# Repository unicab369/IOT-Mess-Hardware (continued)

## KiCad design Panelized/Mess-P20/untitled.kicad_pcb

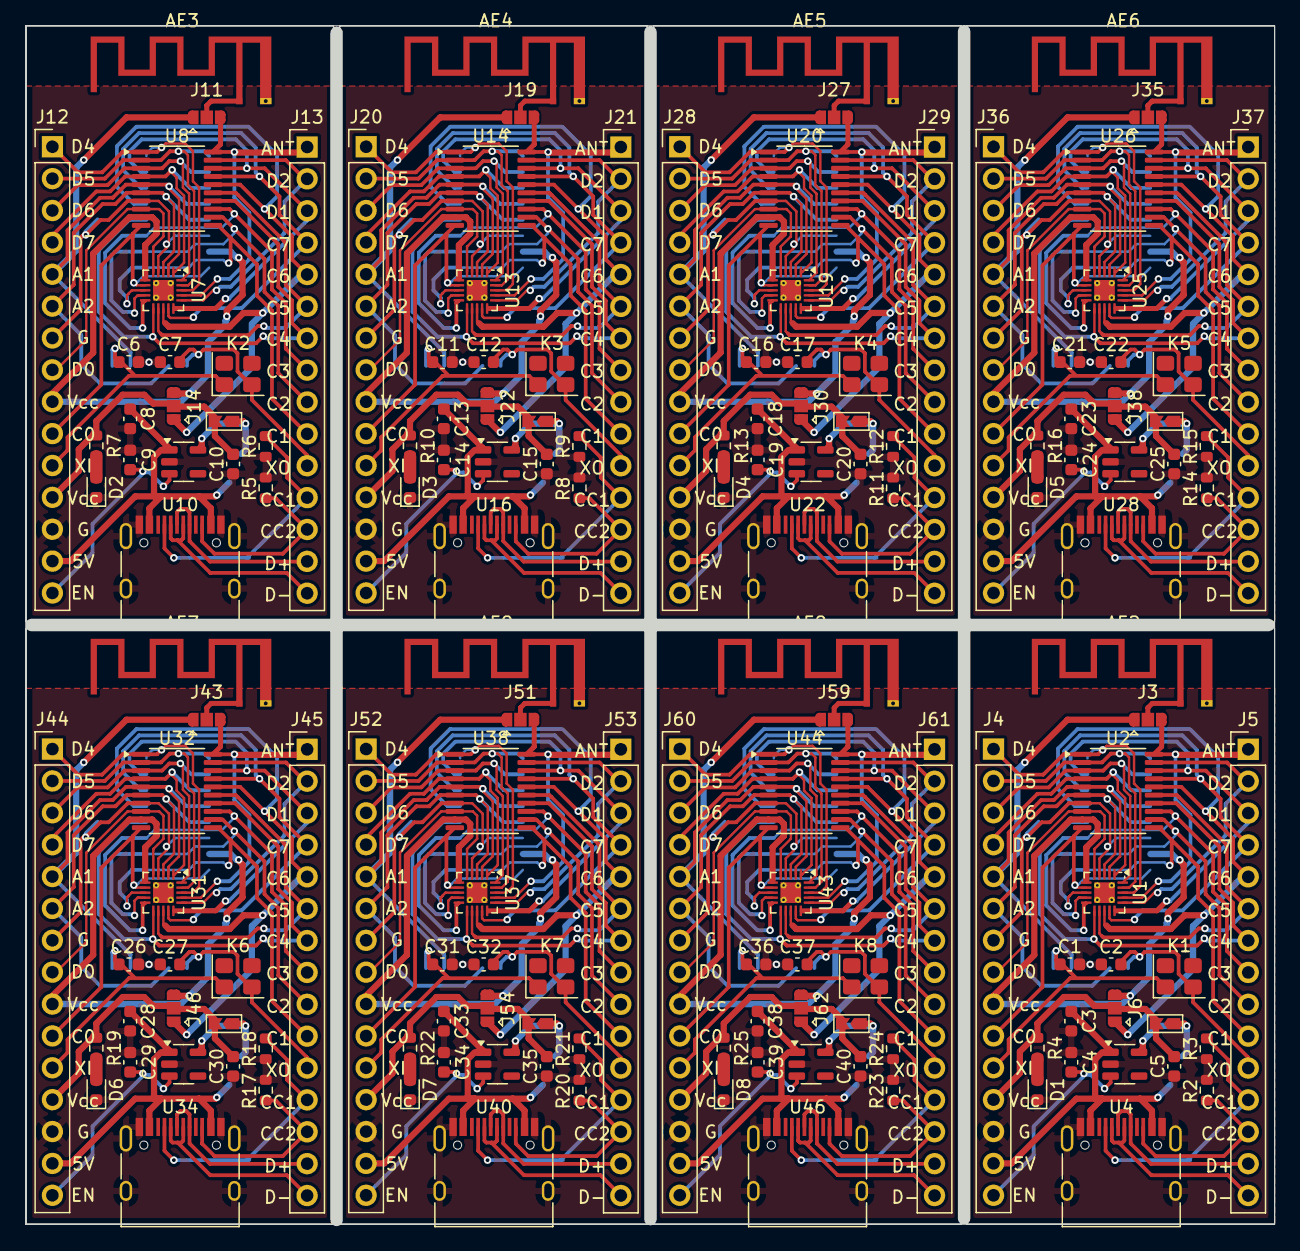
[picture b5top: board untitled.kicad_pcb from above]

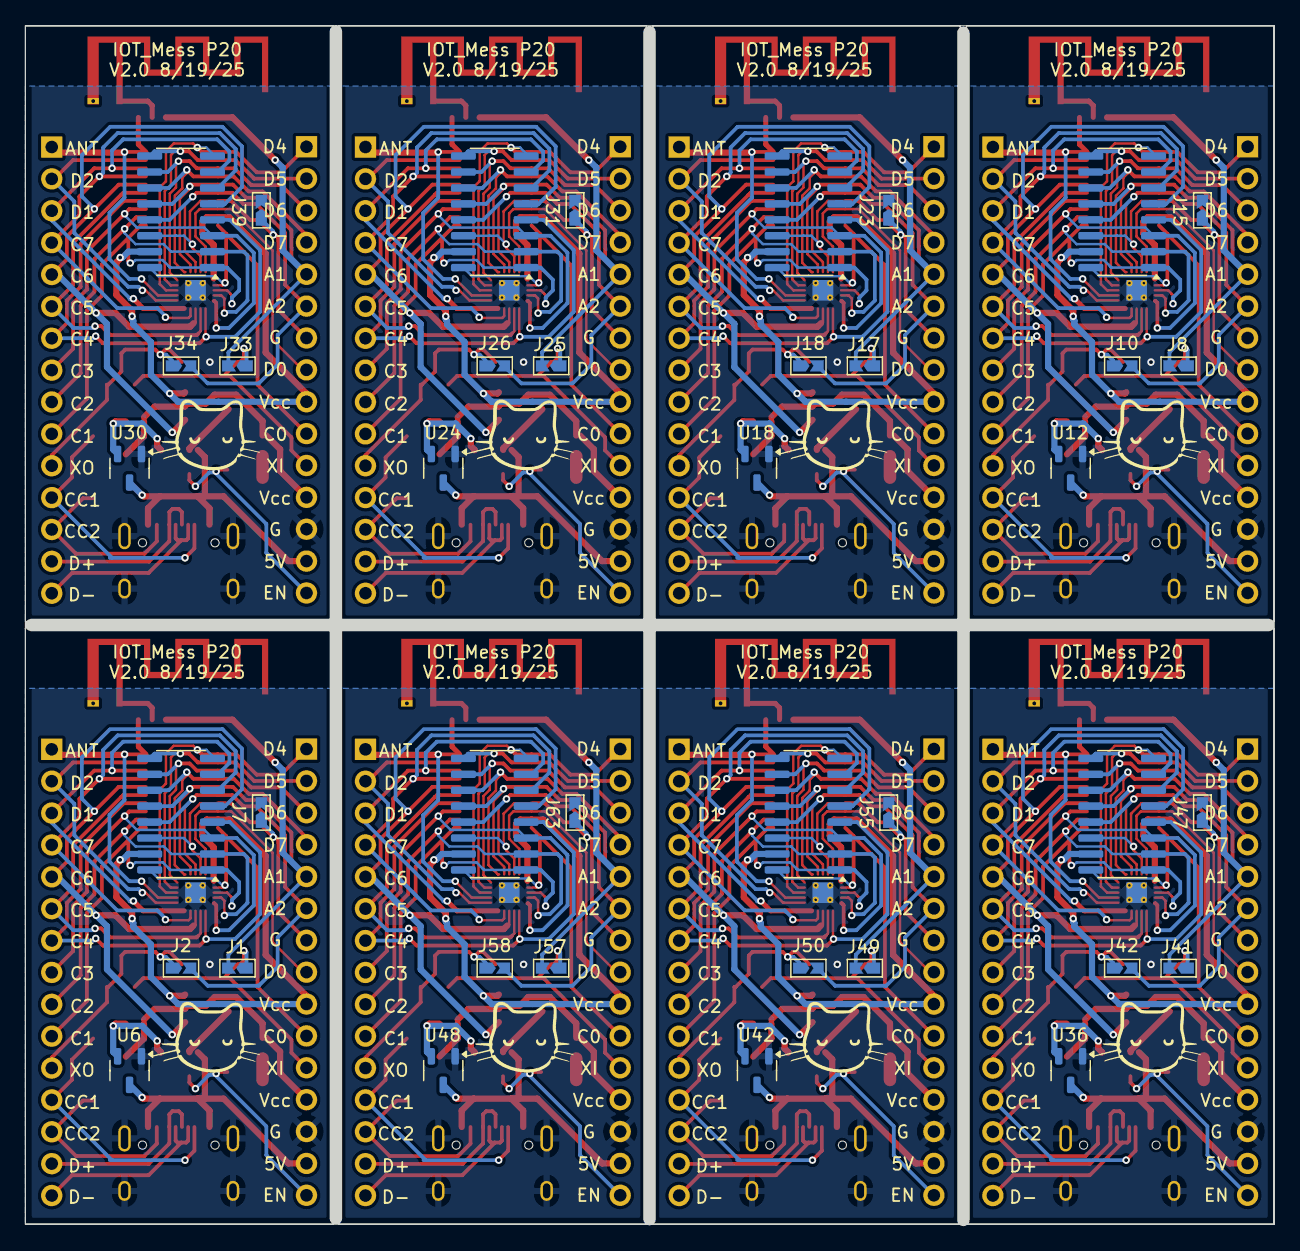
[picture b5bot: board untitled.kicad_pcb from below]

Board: 2 copper layers, 99.5 x 95.5 mm, 200 parts (40 on the bottom side), 33 nets.

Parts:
AE2, AE3, AE4, AE5, AE6, AE7, AE8, AE9: Antenna_Shield; Texas_SWRA117D_2.4GHz_Left
C1, C2, C6, C7, C11, C12, C16, C17, C21, C22, C26, C27, C31, C32, C36, C37: 12-25pF; C_0603_1608Metric
C3, C8, C13, C18, C23, C28, C33, C38: 10u; C_0603_1608Metric
C4, C5, C9, C10, C14, C15, C19, C20, C24, C25, C29, C30, C34, C35, C39, C40: 1u; C_0603_1608Metric
D1, D2, D3, D4, D5, D6, D7, D8: LED; LED_0603_1608Metric
J1, J2, J7, J8, J9, J10, J15, J16, J17, J18, J23, J24, J25, J26, J31, J32, J33, J34, J39, J40, J41, J42, J47, J48, J49, J50, J55, J56, J57, J58, J63, J64: Jumper_2; Jumpper-triangle
J3, J6, J11, J14, J19, J22, J27, J30, J35, J38, J43, J46, J51, J54, J59, J62: Jumper; Jumper-3_P1.3mm_Open_RoundedPad1.0x1.5mm
J4, J5, J12, J13, J20, J21, J28, J29, J36, J37, J44, J45, J52, J53, J60, J61: Conn_01x15_Pin; PinHeader_1x15_P2.54mm_Vertical
K1, K2, K3, K4, K5, K6, K7, K8: Crystal; Crystal_SMD_3225-4Pin_3.2x2.5mm
R2, R3, R5, R6, R8, R9, R11, R12, R14, R15, R17, R18, R20, R21, R23, R24: 5.1K; R_0603_1608Metric
R4, R7, R10, R13, R16, R19, R22, R25: R; R_0603_1608Metric
U1, U7, U13, U19, U25, U31, U37, U43: QFN-20-1EP_3x3mm_P0.4mm_EP1.65x1.65mm_ThermalVias
U2, U8, U14, U20, U26, U32, U38, U44: TSSOP-20_4.4x6.5mm_P0.65mm
U3, U9, U15, U21, U27, U33, U39, U45: SOP-16_3.9x9.9mm_P1.27mm
U4, U10, U16, U22, U28, U34, U40, U46: USB_C_Receptacle_USB2.0_16P; USB_C_Receptacle_HRO_TYPE-C-31-M-12
U5, U11, U17, U23, U29, U35, U41, U47: ME6211C33M5; SOT-23-5
U6, U12, U18, U24, U30, U36, U42, U48: XC6206PxxxMR; SOT-23-3

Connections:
5V: C3.1, C8.1, C13.1, C18.1, C23.1, C28.1, C33.1, C38.1, J4.14, J12.14, J20.14, J28.14, J36.14, J44.14, J52.14, J60.14, U4.A4 (VBUS), U4.A9 (VBUS), U4.B4 (VBUS), U4.B9 (VBUS), U5.1 (V_{IN}), U6.3 (VI), U10.A4 (VBUS), U10.A9 (VBUS), U10.B4 (VBUS), U10.B9 (VBUS), U11.1 (V_{IN}), U12.3 (VI), U16.A4 (VBUS), U16.A9 (VBUS), U16.B4 (VBUS), U16.B9 (VBUS), U17.1 (V_{IN}), U18.3 (VI), U22.A4 (VBUS), U22.A9 (VBUS), U22.B4 (VBUS), U22.B9 (VBUS), U23.1 (V_{IN}), U24.3 (VI), U28.A4 (VBUS), U28.A9 (VBUS), U28.B4 (VBUS), U28.B9 (VBUS), U29.1 (V_{IN}), U30.3 (VI), U34.A4 (VBUS), U34.A9 (VBUS), U34.B4 (VBUS), U34.B9 (VBUS), U35.1 (V_{IN}), U36.3 (VI), U40.A4 (VBUS), U40.A9 (VBUS), U40.B4 (VBUS), U40.B9 (VBUS), U41.1 (V_{IN}), U42.3 (VI), U46.A4 (VBUS), U46.A9 (VBUS), U46.B4 (VBUS), U46.B9 (VBUS), U47.1 (V_{IN}), U48.3 (VI)
+3.3V: C5.1, C10.1, C15.1, C20.1, C25.1, C30.1, C35.1, C40.1, J4.12, J6.2 (C), J9.2 (B), J12.12, J14.2 (C), J16.2 (B), J20.12, J22.2 (C), J24.2 (B), J28.12, J30.2 (C), J32.2 (B), J36.12, J38.2 (C), J40.2 (B), J44.12, J46.2 (C), J48.2 (B), J52.12, J54.2 (C), J56.2 (B), J60.12, J62.2 (C), J64.2 (B), R4.1, R7.1, R10.1, R13.1, R16.1, R19.1, R22.1, R25.1
ANT: AE2.1 (A), AE3.1 (A), AE4.1 (A), AE5.1 (A), AE6.1 (A), AE7.1 (A), AE8.1 (A), AE9.1 (A), J3.2 (C), J11.2 (C), J19.2 (C), J27.2 (C), J35.2 (C), J43.2 (C), J51.2 (C), J59.2 (C)
CC1: J5.12, J13.12, J21.12, J29.12, J37.12, J45.12, J53.12, J61.12, R3.1, R6.1, R9.1, R12.1, R15.1, R18.1, R21.1, R24.1, U4.A5 (CC1), U10.A5 (CC1), U16.A5 (CC1), U22.A5 (CC1), U28.A5 (CC1), U34.A5 (CC1), U40.A5 (CC1), U46.A5 (CC1)
CC2: J5.13, J13.13, J21.13, J29.13, J37.13, J45.13, J53.13, J61.13, R2.1, R5.1, R8.1, R11.1, R14.1, R17.1, R20.1, R23.1, U4.B5 (CC2), U10.B5 (CC2), U16.B5 (CC2), U22.B5 (CC2), U28.B5 (CC2), U34.B5 (CC2), U40.B5 (CC2), U46.B5 (CC2)
D+: J5.14, J13.14, J21.14, J29.14, J37.14, J45.14, J53.14, J61.14, U4.A6 (D+), U4.B6 (D+), U10.A6 (D+), U10.B6 (D+), U16.A6 (D+), U16.B6 (D+), U22.A6 (D+), U22.B6 (D+), U28.A6 (D+), U28.B6 (D+), U34.A6 (D+), U34.B6 (D+), U40.A6 (D+), U40.B6 (D+), U46.A6 (D+), U46.B6 (D+)
D-: J5.15, J13.15, J21.15, J29.15, J37.15, J45.15, J53.15, J61.15, U4.A7 (D-), U4.B7 (D-), U10.A7 (D-), U10.B7 (D-), U16.A7 (D-), U16.B7 (D-), U22.A7 (D-), U22.B7 (D-), U28.A7 (D-), U28.B7 (D-), U34.A7 (D-), U34.B7 (D-), U40.A7 (D-), U40.B7 (D-), U46.A7 (D-), U46.B7 (D-)
LDO_EN: C4.1, C9.1, C14.1, C19.1, C24.1, C29.1, C34.1, C39.1, J4.15, J12.15, J20.15, J28.15, J36.15, J44.15, J52.15, J60.15, U5.3 (CE), U11.3 (CE), U17.3 (CE), U23.3 (CE), U29.3 (CE), U35.3 (CE), U41.3 (CE), U47.3 (CE)
unnamed: D1.2 (A), D2.2 (A), D3.2 (A), D4.2 (A), D5.2 (A), D6.2 (A), D7.2 (A), D8.2 (A), R4.2, R7.2, R10.2, R13.2, R16.2, R19.2, R22.2, R25.2
unnamed: J9.1 (A), J16.1 (A), J24.1 (A), J32.1 (A), J40.1 (A), J48.1 (A), J56.1 (A), J64.1 (A), U5.5 (V_{OUT}), U6.2 (VO), U11.5 (V_{OUT}), U12.2 (VO), U17.5 (V_{OUT}), U18.2 (VO), U23.5 (V_{OUT}), U24.2 (VO), U29.5 (V_{OUT}), U30.2 (VO), U35.5 (V_{OUT}), U36.2 (VO), U41.5 (V_{OUT}), U42.2 (VO), U47.5 (V_{OUT}), U48.2 (VO)
OSCI: C1.1, C6.1, C11.1, C16.1, C21.1, C26.1, C31.1, C36.1, J1.1 (A), J4.11, J8.1 (A), J12.11, J17.1 (A), J20.11, J25.1 (A), J28.11, J33.1 (A), J36.11, J41.1 (A), J44.11, J49.1 (A), J52.11, J57.1 (A), J60.11, K1.1, K2.1, K3.1, K4.1, K5.1, K6.1, K7.1, K8.1
OSCO: C2.1, C7.1, C12.1, C17.1, C22.1, C27.1, C32.1, C37.1, J2.1 (A), J5.11, J10.1 (A), J13.11, J18.1 (A), J21.11, J26.1 (A), J29.11, J34.1 (A), J37.11, J42.1 (A), J45.11, J50.1 (A), J53.11, J58.1 (A), J61.11, K1.2, K2.2, K3.2, K4.2, K5.2, K6.2, K7.2, K8.2
P_0: C1.2, C2.2, C3.2, C4.2, C5.2, C6.2, C7.2, C8.2, C9.2, C10.2, C11.2, C12.2, C13.2, C14.2, C15.2, C16.2, C17.2, C18.2, C19.2, C20.2, C21.2, C22.2, C23.2, C24.2, C25.2, C26.2, C27.2, C28.2, C29.2, C30.2, C31.2, C32.2, C33.2, C34.2, C35.2, C36.2, C37.2, C38.2, C39.2, C40.2, D1.1 (K), D2.1 (K), D3.1 (K), D4.1 (K), D5.1 (K), D6.1 (K), D7.1 (K), D8.1 (K), J4.13, J7.2 (B), J12.13, J15.2 (B), J20.13, J23.2 (B), J28.13, J31.2 (B), J36.13, J39.2 (B), J44.13, J47.2 (B), J52.13, J55.2 (B), J60.13, J63.2 (B), R2.2, R3.2, R5.2, R6.2, R8.2, R9.2, R11.2, R12.2, R14.2, R15.2, R17.2, R18.2, R20.2, R21.2, R23.2, R24.2, U1.21 (GND), U4.A1 (GND), U4.A12 (GND), U4.B1 (GND), U4.B12 (GND), U4.S1 (SHIELD), U5.2 (V_{SS}), U6.1 (GND), U7.21 (GND), U10.A1 (GND), U10.A12 (GND), U10.B1 (GND), U10.B12 (GND), U10.S1 (SHIELD), U11.2 (V_{SS}), U12.1 (GND), U13.21 (GND), U16.A1 (GND), U16.A12 (GND), U16.B1 (GND), U16.B12 (GND), U16.S1 (SHIELD), U17.2 (V_{SS}), U18.1 (GND), U19.21 (GND), U22.A1 (GND), U22.A12 (GND), U22.B1 (GND), U22.B12 (GND), U22.S1 (SHIELD), U23.2 (V_{SS}), U24.1 (GND), U25.21 (GND), U28.A1 (GND), U28.A12 (GND), U28.B1 (GND), U28.B12 (GND), U28.S1 (SHIELD), U29.2 (V_{SS}), U30.1 (GND), U31.21 (GND), U34.A1 (GND), U34.A12 (GND), U34.B1 (GND), U34.B12 (GND), U34.S1 (SHIELD), U35.2 (V_{SS}), U36.1 (GND), U37.21 (GND), U40.A1 (GND), U40.A12 (GND), U40.B1 (GND), U40.B12 (GND), U40.S1 (SHIELD), U41.2 (V_{SS}), U42.1 (GND), U43.21 (GND), U46.A1 (GND), U46.A12 (GND), U46.B1 (GND), U46.B12 (GND), U46.S1 (SHIELD), U47.2 (V_{SS}), U48.1 (GND)
P_1: J4.1, J12.1, J20.1, J28.1, J36.1, J44.1, J52.1, J60.1, U1.18 (PD4/A7), U2.1 (PD4/A7), U3.8 (PD4/A7), U7.18 (PD4/A7), U8.1 (PD4/A7), U9.8 (PD4/A7), U13.18 (PD4/A7), U14.1 (PD4/A7), U15.8 (PD4/A7), U19.18 (PD4/A7), U20.1 (PD4/A7), U21.8 (PD4/A7), U25.18 (PD4/A7), U26.1 (PD4/A7), U27.8 (PD4/A7), U31.18 (PD4/A7), U32.1 (PD4/A7), U33.8 (PD4/A7), U37.18 (PD4/A7), U38.1 (PD4/A7), U39.8 (PD4/A7), U43.18 (PD4/A7), U44.1 (PD4/A7), U45.8 (PD4/A7)
P_2: J4.2, J12.2, J20.2, J28.2, J36.2, J44.2, J52.2, J60.2, U1.19 (PD5/A5/UTX/VDD*), U2.2 (PD5/A5/OSCI*), U3.9 (PD5/A5/UTX), U7.19 (PD5/A5/UTX/VDD*), U8.2 (PD5/A5/OSCI*), U9.9 (PD5/A5/UTX), U13.19 (PD5/A5/UTX/VDD*), U14.2 (PD5/A5/OSCI*), U15.9 (PD5/A5/UTX), U19.19 (PD5/A5/UTX/VDD*), U20.2 (PD5/A5/OSCI*), U21.9 (PD5/A5/UTX), U25.19 (PD5/A5/UTX/VDD*), U26.2 (PD5/A5/OSCI*), U27.9 (PD5/A5/UTX), U31.19 (PD5/A5/UTX/VDD*), U32.2 (PD5/A5/OSCI*), U33.9 (PD5/A5/UTX), U37.19 (PD5/A5/UTX/VDD*), U38.2 (PD5/A5/OSCI*), U39.9 (PD5/A5/UTX), U43.19 (PD5/A5/UTX/VDD*), U44.2 (PD5/A5/OSCI*), U45.9 (PD5/A5/UTX)
P_3: J4.3, J12.3, J20.3, J28.3, J36.3, J44.3, J52.3, J60.3, U1.20 (PD6/A6/URX/ANT*), U2.3 (PD6/A6/OSCO*), U3.10 (PD6/A6/URX), U7.20 (PD6/A6/URX/ANT*), U8.3 (PD6/A6/OSCO*), U9.10 (PD6/A6/URX), U13.20 (PD6/A6/URX/ANT*), U14.3 (PD6/A6/OSCO*), U15.10 (PD6/A6/URX), U19.20 (PD6/A6/URX/ANT*), U20.3 (PD6/A6/OSCO*), U21.10 (PD6/A6/URX), U25.20 (PD6/A6/URX/ANT*), U26.3 (PD6/A6/OSCO*), U27.10 (PD6/A6/URX), U31.20 (PD6/A6/URX/ANT*), U32.3 (PD6/A6/OSCO*), U33.10 (PD6/A6/URX), U37.20 (PD6/A6/URX/ANT*), U38.3 (PD6/A6/OSCO*), U39.10 (PD6/A6/URX), U43.20 (PD6/A6/URX/ANT*), U44.3 (PD6/A6/OSCO*), U45.10 (PD6/A6/URX)
P_4: J4.4, J12.4, J20.4, J28.4, J36.4, J44.4, J52.4, J60.4, U1.1 (PD7/NRST), U2.4 (PD7/RST), U3.11 (PD7/NRST), U7.1 (PD7/NRST), U8.4 (PD7/RST), U9.11 (PD7/NRST), U13.1 (PD7/NRST), U14.4 (PD7/RST), U15.11 (PD7/NRST), U19.1 (PD7/NRST), U20.4 (PD7/RST), U21.11 (PD7/NRST), U25.1 (PD7/NRST), U26.4 (PD7/RST), U27.11 (PD7/NRST), U31.1 (PD7/NRST), U32.4 (PD7/RST), U33.11 (PD7/NRST), U37.1 (PD7/NRST), U38.4 (PD7/RST), U39.11 (PD7/NRST), U43.1 (PD7/NRST), U44.4 (PD7/RST), U45.11 (PD7/NRST)
P_5: J1.2 (B), J3.1 (A), J4.5, J8.2 (B), J11.1 (A), J12.5, J17.2 (B), J19.1 (A), J20.5, J25.2 (B), J27.1 (A), J28.5, J33.2 (B), J35.1 (A), J36.5, J41.2 (B), J43.1 (A), J44.5, J49.2 (B), J51.1 (A), J52.5, J57.2 (B), J59.1 (A), J60.5, U1.2 (PA1/OSCI), U2.5 (PA1/OSCI), U3.12 (PA1/A1/OSC_IN), U7.2 (PA1/OSCI), U8.5 (PA1/OSCI), U9.12 (PA1/A1/OSC_IN), U13.2 (PA1/OSCI), U14.5 (PA1/OSCI), U15.12 (PA1/A1/OSC_IN), U19.2 (PA1/OSCI), U20.5 (PA1/OSCI), U21.12 (PA1/A1/OSC_IN), U25.2 (PA1/OSCI), U26.5 (PA1/OSCI), U27.12 (PA1/A1/OSC_IN), U31.2 (PA1/OSCI), U32.5 (PA1/OSCI), U33.12 (PA1/A1/OSC_IN), U37.2 (PA1/OSCI), U38.5 (PA1/OSCI), U39.12 (PA1/A1/OSC_IN), U43.2 (PA1/OSCI), U44.5 (PA1/OSCI), U45.12 (PA1/A1/OSC_IN)
P_6: J2.2 (B), J4.6, J10.2 (B), J12.6, J18.2 (B), J20.6, J26.2 (B), J28.6, J34.2 (B), J36.6, J42.2 (B), J44.6, J50.2 (B), J52.6, J58.2 (B), J60.6, U1.3 (PA2/OSCO), U2.6 (PA2/OSCO), U3.13 (PA2/A0/OSC_OUT), U7.3 (PA2/OSCO), U8.6 (PA2/OSCO), U9.13 (PA2/A0/OSC_OUT), U13.3 (PA2/OSCO), U14.6 (PA2/OSCO), U15.13 (PA2/A0/OSC_OUT), U19.3 (PA2/OSCO), U20.6 (PA2/OSCO), U21.13 (PA2/A0/OSC_OUT), U25.3 (PA2/OSCO), U26.6 (PA2/OSCO), U27.13 (PA2/A0/OSC_OUT), U31.3 (PA2/OSCO), U32.6 (PA2/OSCO), U33.13 (PA2/A0/OSC_OUT), U37.3 (PA2/OSCO), U38.6 (PA2/OSCO), U39.13 (PA2/A0/OSC_OUT), U43.3 (PA2/OSCO), U44.6 (PA2/OSCO), U45.13 (PA2/A0/OSC_OUT)
P_7: J4.7, J7.1 (A), J12.7, J15.1 (A), J20.7, J23.1 (A), J28.7, J31.1 (A), J36.7, J39.1 (A), J44.7, J47.1 (A), J52.7, J55.1 (A), J60.7, J63.1 (A), U1.4 (VSS), U2.7 (VSS), U3.14 (GND), U7.4 (VSS), U8.7 (VSS), U9.14 (GND), U13.4 (VSS), U14.7 (VSS), U15.14 (GND), U19.4 (VSS), U20.7 (VSS), U21.14 (GND), U25.4 (VSS), U26.7 (VSS), U27.14 (GND), U31.4 (VSS), U32.7 (VSS), U33.14 (GND), U37.4 (VSS), U38.7 (VSS), U39.14 (GND), U43.4 (VSS), U44.7 (VSS), U45.14 (GND)
P_8: J4.8, J12.8, J20.8, J28.8, J36.8, J44.8, J52.8, J60.8, U1.5 (PD0/ANT*(57x)), U2.8 (PD0), U7.5 (PD0/ANT*(57x)), U8.8 (PD0), U13.5 (PD0/ANT*(57x)), U14.8 (PD0), U19.5 (PD0/ANT*(57x)), U20.8 (PD0), U25.5 (PD0/ANT*(57x)), U26.8 (PD0), U31.5 (PD0/ANT*(57x)), U32.8 (PD0), U37.5 (PD0/ANT*(57x)), U38.8 (PD0), U43.5 (PD0/ANT*(57x)), U44.8 (PD0)
P_9: J4.9, J6.3 (B), J12.9, J14.3 (B), J20.9, J22.3 (B), J28.9, J30.3 (B), J36.9, J38.3 (B), J44.9, J46.3 (B), J52.9, J54.3 (B), J60.9, J62.3 (B), U1.6 (VDD), U2.9 (VDD), U3.15 (VDD), U7.6 (VDD), U8.9 (VDD), U9.15 (VDD), U13.6 (VDD), U14.9 (VDD), U15.15 (VDD), U19.6 (VDD), U20.9 (VDD), U21.15 (VDD), U25.6 (VDD), U26.9 (VDD), U27.15 (VDD), U31.6 (VDD), U32.9 (VDD), U33.15 (VDD), U37.6 (VDD), U38.9 (VDD), U39.15 (VDD), U43.6 (VDD), U44.9 (VDD), U45.15 (VDD)
P_10: J4.10, J12.10, J20.10, J28.10, J36.10, J44.10, J52.10, J60.10, U1.7 (PC0), U2.10 (PC0), U3.16 (PC0), U7.7 (PC0), U8.10 (PC0), U9.16 (PC0), U13.7 (PC0), U14.10 (PC0), U15.16 (PC0), U19.7 (PC0), U20.10 (PC0), U21.16 (PC0), U25.7 (PC0), U26.10 (PC0), U27.16 (PC0), U31.7 (PC0), U32.10 (PC0), U33.16 (PC0), U37.7 (PC0), U38.10 (PC0), U39.16 (PC0), U43.7 (PC0), U44.10 (PC0), U45.16 (PC0)
P_11: J5.10, J13.10, J21.10, J29.10, J37.10, J45.10, J53.10, J61.10, U1.8 (PC1/SDA), U2.11 (PC1/SDA), U3.1 (PC1/SDA), U7.8 (PC1/SDA), U8.11 (PC1/SDA), U9.1 (PC1/SDA), U13.8 (PC1/SDA), U14.11 (PC1/SDA), U15.1 (PC1/SDA), U19.8 (PC1/SDA), U20.11 (PC1/SDA), U21.1 (PC1/SDA), U25.8 (PC1/SDA), U26.11 (PC1/SDA), U27.1 (PC1/SDA), U31.8 (PC1/SDA), U32.11 (PC1/SDA), U33.1 (PC1/SDA), U37.8 (PC1/SDA), U38.11 (PC1/SDA), U39.1 (PC1/SDA), U43.8 (PC1/SDA), U44.11 (PC1/SDA), U45.1 (PC1/SDA)
P_12: J5.9, J13.9, J21.9, J29.9, J37.9, J45.9, J53.9, J61.9, U1.9 (PC2/SCL), U2.12 (PC2/SCL), U3.2 (PC2/SCL), U7.9 (PC2/SCL), U8.12 (PC2/SCL), U9.2 (PC2/SCL), U13.9 (PC2/SCL), U14.12 (PC2/SCL), U15.2 (PC2/SCL), U19.9 (PC2/SCL), U20.12 (PC2/SCL), U21.2 (PC2/SCL), U25.9 (PC2/SCL), U26.12 (PC2/SCL), U27.2 (PC2/SCL), U31.9 (PC2/SCL), U32.12 (PC2/SCL), U33.2 (PC2/SCL), U37.9 (PC2/SCL), U38.12 (PC2/SCL), U39.2 (PC2/SCL), U43.9 (PC2/SCL), U44.12 (PC2/SCL), U45.2 (PC2/SCL)
P_13: J5.8, J13.8, J21.8, J29.8, J37.8, J45.8, J53.8, J61.8, U1.10 (PC3/RST*), U2.13 (PC3), U3.3 (PC3), U7.10 (PC3/RST*), U8.13 (PC3), U9.3 (PC3), U13.10 (PC3/RST*), U14.13 (PC3), U15.3 (PC3), U19.10 (PC3/RST*), U20.13 (PC3), U21.3 (PC3), U25.10 (PC3/RST*), U26.13 (PC3), U27.3 (PC3), U31.10 (PC3/RST*), U32.13 (PC3), U33.3 (PC3), U37.10 (PC3/RST*), U38.13 (PC3), U39.3 (PC3), U43.10 (PC3/RST*), U44.13 (PC3), U45.3 (PC3)
P_14: J5.7, J13.7, J21.7, J29.7, J37.7, J45.7, J53.7, J61.7, U1.11 (PC4/A2), U2.14 (PC4/A2), U3.4 (PC4/A2), U7.11 (PC4/A2), U8.14 (PC4/A2), U9.4 (PC4/A2), U13.11 (PC4/A2), U14.14 (PC4/A2), U15.4 (PC4/A2), U19.11 (PC4/A2), U20.14 (PC4/A2), U21.4 (PC4/A2), U25.11 (PC4/A2), U26.14 (PC4/A2), U27.4 (PC4/A2), U31.11 (PC4/A2), U32.14 (PC4/A2), U33.4 (PC4/A2), U37.11 (PC4/A2), U38.14 (PC4/A2), U39.4 (PC4/A2), U43.11 (PC4/A2), U44.14 (PC4/A2), U45.4 (PC4/A2)
P_15: J5.6, J13.6, J21.6, J29.6, J37.6, J45.6, J53.6, J61.6, U1.12 (PC5/X32MO*), U2.15 (PC5/VSS*), U7.12 (PC5/X32MO*), U8.15 (PC5/VSS*), U13.12 (PC5/X32MO*), U14.15 (PC5/VSS*), U19.12 (PC5/X32MO*), U20.15 (PC5/VSS*), U25.12 (PC5/X32MO*), U26.15 (PC5/VSS*), U31.12 (PC5/X32MO*), U32.15 (PC5/VSS*), U37.12 (PC5/X32MO*), U38.15 (PC5/VSS*), U43.12 (PC5/X32MO*), U44.15 (PC5/VSS*)
P_16: J5.5, J6.1 (A), J13.5, J14.1 (A), J21.5, J22.1 (A), J29.5, J30.1 (A), J37.5, J38.1 (A), J45.5, J46.1 (A), J53.5, J54.1 (A), J61.5, J62.1 (A), U1.13 (PC6/MOSI/X32MI*), U2.16 (PC6/MOSI/VDD*), U3.5 (PC6/MOSI), U7.13 (PC6/MOSI/X32MI*), U8.16 (PC6/MOSI/VDD*), U9.5 (PC6/MOSI), U13.13 (PC6/MOSI/X32MI*), U14.16 (PC6/MOSI/VDD*), U15.5 (PC6/MOSI), U19.13 (PC6/MOSI/X32MI*), U20.16 (PC6/MOSI/VDD*), U21.5 (PC6/MOSI), U25.13 (PC6/MOSI/X32MI*), U26.16 (PC6/MOSI/VDD*), U27.5 (PC6/MOSI), U31.13 (PC6/MOSI/X32MI*), U32.16 (PC6/MOSI/VDD*), U33.5 (PC6/MOSI), U37.13 (PC6/MOSI/X32MI*), U38.16 (PC6/MOSI/VDD*), U39.5 (PC6/MOSI), U43.13 (PC6/MOSI/X32MI*), U44.16 (PC6/MOSI/VDD*), U45.5 (PC6/MOSI)
P_17: J5.4, J13.4, J21.4, J29.4, J37.4, J45.4, J53.4, J61.4, U1.14 (PC7/MISO), U2.17 (PC7/MISO/UDM*), U3.6 (PC7/MISO), U7.14 (PC7/MISO), U8.17 (PC7/MISO/UDM*), U9.6 (PC7/MISO), U13.14 (PC7/MISO), U14.17 (PC7/MISO/UDM*), U15.6 (PC7/MISO), U19.14 (PC7/MISO), U20.17 (PC7/MISO/UDM*), U21.6 (PC7/MISO), U25.14 (PC7/MISO), U26.17 (PC7/MISO/UDM*), U27.6 (PC7/MISO), U31.14 (PC7/MISO), U32.17 (PC7/MISO/UDM*), U33.6 (PC7/MISO), U37.14 (PC7/MISO), U38.17 (PC7/MISO/UDM*), U39.6 (PC7/MISO), U43.14 (PC7/MISO), U44.17 (PC7/MISO/UDM*), U45.6 (PC7/MISO)
P_18: J5.3, J13.3, J21.3, J29.3, J37.3, J45.3, J53.3, J61.3, U1.15 (PD1/SWIO/ANT*), U2.18 (PD1/SWIO/UDP*), U3.7 (PD1/SWIO), U7.15 (PD1/SWIO/ANT*), U8.18 (PD1/SWIO/UDP*), U9.7 (PD1/SWIO), U13.15 (PD1/SWIO/ANT*), U14.18 (PD1/SWIO/UDP*), U15.7 (PD1/SWIO), U19.15 (PD1/SWIO/ANT*), U20.18 (PD1/SWIO/UDP*), U21.7 (PD1/SWIO), U25.15 (PD1/SWIO/ANT*), U26.18 (PD1/SWIO/UDP*), U27.7 (PD1/SWIO), U31.15 (PD1/SWIO/ANT*), U32.18 (PD1/SWIO/UDP*), U33.7 (PD1/SWIO), U37.15 (PD1/SWIO/ANT*), U38.18 (PD1/SWIO/UDP*), U39.7 (PD1/SWIO), U43.15 (PD1/SWIO/ANT*), U44.18 (PD1/SWIO/UDP*), U45.7 (PD1/SWIO)
P_19: J5.2, J13.2, J21.2, J29.2, J37.2, J45.2, J53.2, J61.2, U1.16 (PD2/A3/UDP*), U2.19 (PD2/A3/SWIO*), U7.16 (PD2/A3/UDP*), U8.19 (PD2/A3/SWIO*), U13.16 (PD2/A3/UDP*), U14.19 (PD2/A3/SWIO*), U19.16 (PD2/A3/UDP*), U20.19 (PD2/A3/SWIO*), U25.16 (PD2/A3/UDP*), U26.19 (PD2/A3/SWIO*), U31.16 (PD2/A3/UDP*), U32.19 (PD2/A3/SWIO*), U37.16 (PD2/A3/UDP*), U38.19 (PD2/A3/SWIO*), U43.16 (PD2/A3/UDP*), U44.19 (PD2/A3/SWIO*)
P_20: J3.3 (B), J5.1, J11.3 (B), J13.1, J19.3 (B), J21.1, J27.3 (B), J29.1, J35.3 (B), J37.1, J43.3 (B), J45.1, J51.3 (B), J53.1, J59.3 (B), J61.1, U1.17 (PD3/A4/UDM*), U2.20 (PD3/A4/ANT*), U7.17 (PD3/A4/UDM*), U8.20 (PD3/A4/ANT*), U13.17 (PD3/A4/UDM*), U14.20 (PD3/A4/ANT*), U19.17 (PD3/A4/UDM*), U20.20 (PD3/A4/ANT*), U25.17 (PD3/A4/UDM*), U26.20 (PD3/A4/ANT*), U31.17 (PD3/A4/UDM*), U32.20 (PD3/A4/ANT*), U37.17 (PD3/A4/UDM*), U38.20 (PD3/A4/ANT*), U43.17 (PD3/A4/UDM*), U44.20 (PD3/A4/ANT*)
